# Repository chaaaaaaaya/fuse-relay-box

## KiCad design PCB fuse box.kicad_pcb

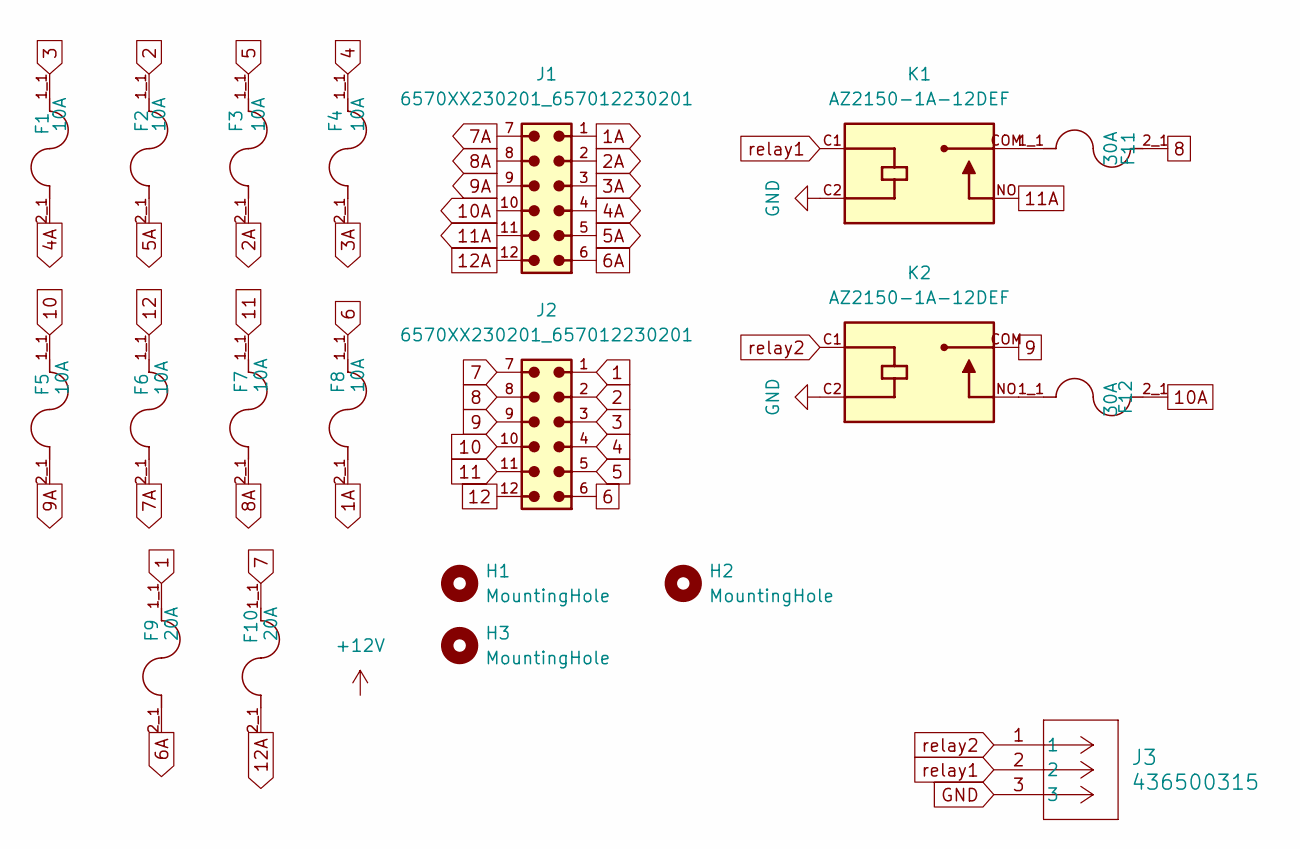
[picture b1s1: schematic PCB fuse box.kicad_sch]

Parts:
F1, F2, F3, F4, F5, F6, F7, F8: 10A; CONN_3557-2_KEY; PARTREV D
F9, F10: 20A; CONN_3557-2_KEY; PARTREV D
F11, F12: 30A; CONN_3557-2_KEY; PARTREV D
H1, H2, H3: MountingHole; MountingHole_2.2mm_M2_Pad
J1, J2: 6570XX230201_657012230201; 657012230201
J3: 436500315; CONN_SD-43650-006_03_MOL
K1, K2: AZ2150-1A-12DEF; RELAY_AZ2150-1A-12DEF; PARTREV 2022-05-21

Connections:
1: F9.1_1, F9.1_2, J2.1
1A: F8.2_1, F8.2_2, J1.1
2: F2.1_1, F2.1_2, J2.2
2A: F3.2_1, F3.2_2, J1.2
3: F1.1_1, F1.1_2, J2.3
3A: F4.2_1, F4.2_2, J1.3
4: F4.1_1, F4.1_2, J2.4
4A: F1.2_1, F1.2_2, J1.4
5: F3.1_1, F3.1_2, J2.5
5A: F2.2_1, F2.2_2, J1.5
6: F8.1_1, F8.1_2, J2.6
6A: F9.2_1, F9.2_2, J1.6
7: F10.1_1, F10.1_2, J2.7
7A: F6.2_1, F6.2_2, J1.7
8: F11.2_1, F11.2_2, J2.8
8A: F7.2_1, F7.2_2, J1.8
9: J2.9, K2.COM
9A: F5.2_1, F5.2_2, J1.9
10: F5.1_1, F5.1_2, J2.10
10A: F12.2_1, F12.2_2, J1.10
11: F7.1_1, F7.1_2, J2.11
11A: J1.11, K1.NO
12: F6.1_1, F6.1_2, J2.12
12A: F10.2_1, F10.2_2, J1.12
GND: J3.3, K1.C2, K2.C2
unnamed: F11.1_1, F11.1_2, K1.COM
unnamed: F12.1_1, F12.1_2, K2.NO
relay1: J3.2, K1.C1
relay2: J3.1, K2.C1

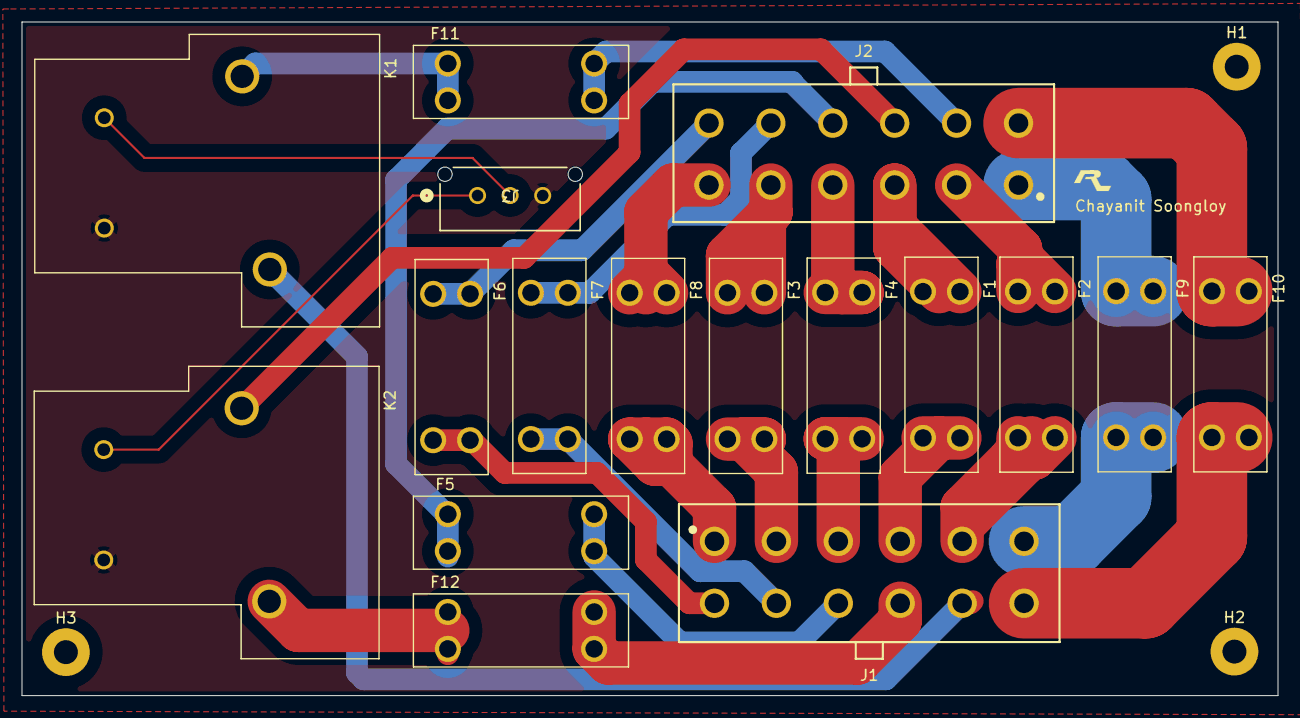
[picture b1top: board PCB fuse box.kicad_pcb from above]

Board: 2 copper layers, 115.6 x 62.0 mm, 20 parts (0 on the bottom side), 29 nets.
